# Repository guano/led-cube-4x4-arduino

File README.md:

# led-cube-4x4-arduino
This is all the files for my 4x4 led cube, programmed by arduino. Also has a pcb design file for to make it a shield.

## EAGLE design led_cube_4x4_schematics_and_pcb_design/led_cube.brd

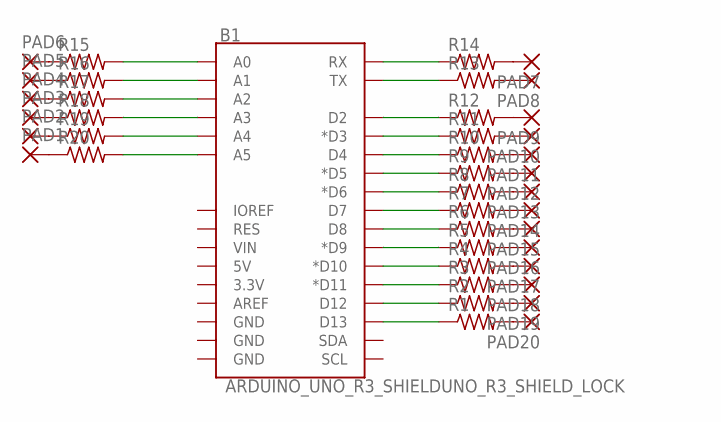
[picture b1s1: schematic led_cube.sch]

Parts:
B1: ARDUINO_UNO_R3_SHIELDUNO_R3_SHIELD_LOCK; UNO_R3_SHIELD_LOCK
PAD1, PAD2, PAD3, PAD4, PAD5, PAD6, PAD7, PAD8, PAD9, PAD10, PAD11, PAD12, PAD13, PAD14, PAD15, PAD16, PAD17, PAD18, PAD19, PAD20: 3,81/1,1
R1, R2, R3, R4, R5, R6, R7, R8, R9, R10, R11, R12, R13, R14, R15, R16, R17, R18, R19, R20: R-US_0204/7; 0204/7

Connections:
unnamed: PAD1.1, R20.1
unnamed: PAD2.1, R19.1
unnamed: PAD3.1, R18.1
unnamed: PAD4.1, R17.1
unnamed: PAD5.1, R16.1
unnamed: PAD6.1, R15.1
unnamed: PAD7.1, R14.2
unnamed: PAD8.1, R13.2
unnamed: PAD9.1, R12.2
unnamed: PAD10.1, R11.2
unnamed: PAD11.1, R10.2
unnamed: PAD12.1, R9.2
unnamed: PAD13.1, R8.2
unnamed: PAD14.1, R7.2
unnamed: PAD15.1, R6.2
unnamed: PAD16.1, R5.2
unnamed: PAD17.1, R4.2
unnamed: PAD18.1, R3.2
unnamed: PAD19.1, R2.2
unnamed: PAD20.1, R1.2
unnamed: B1.A0, R15.2
unnamed: B1.A1, R16.2
unnamed: B1.A2, R17.2
unnamed: B1.A3, R18.2
unnamed: B1.A4, R19.2
unnamed: B1.A5, R20.2
unnamed: B1.RX, R14.1
unnamed: B1.TX, R13.1
unnamed: B1.D2, R12.1
unnamed: B1.D3 (*D3), R11.1
unnamed: B1.D4, R10.1
unnamed: B1.D5 (*D5), R9.1
unnamed: B1.D6 (*D6), R8.1
unnamed: B1.D7, R7.1
unnamed: B1.D8, R6.1
unnamed: B1.D9 (*D9), R5.1
unnamed: B1.D10 (*D10), R4.1
unnamed: B1.D11 (*D11), R3.1
unnamed: B1.D12, R2.1
unnamed: B1.D13, R1.1

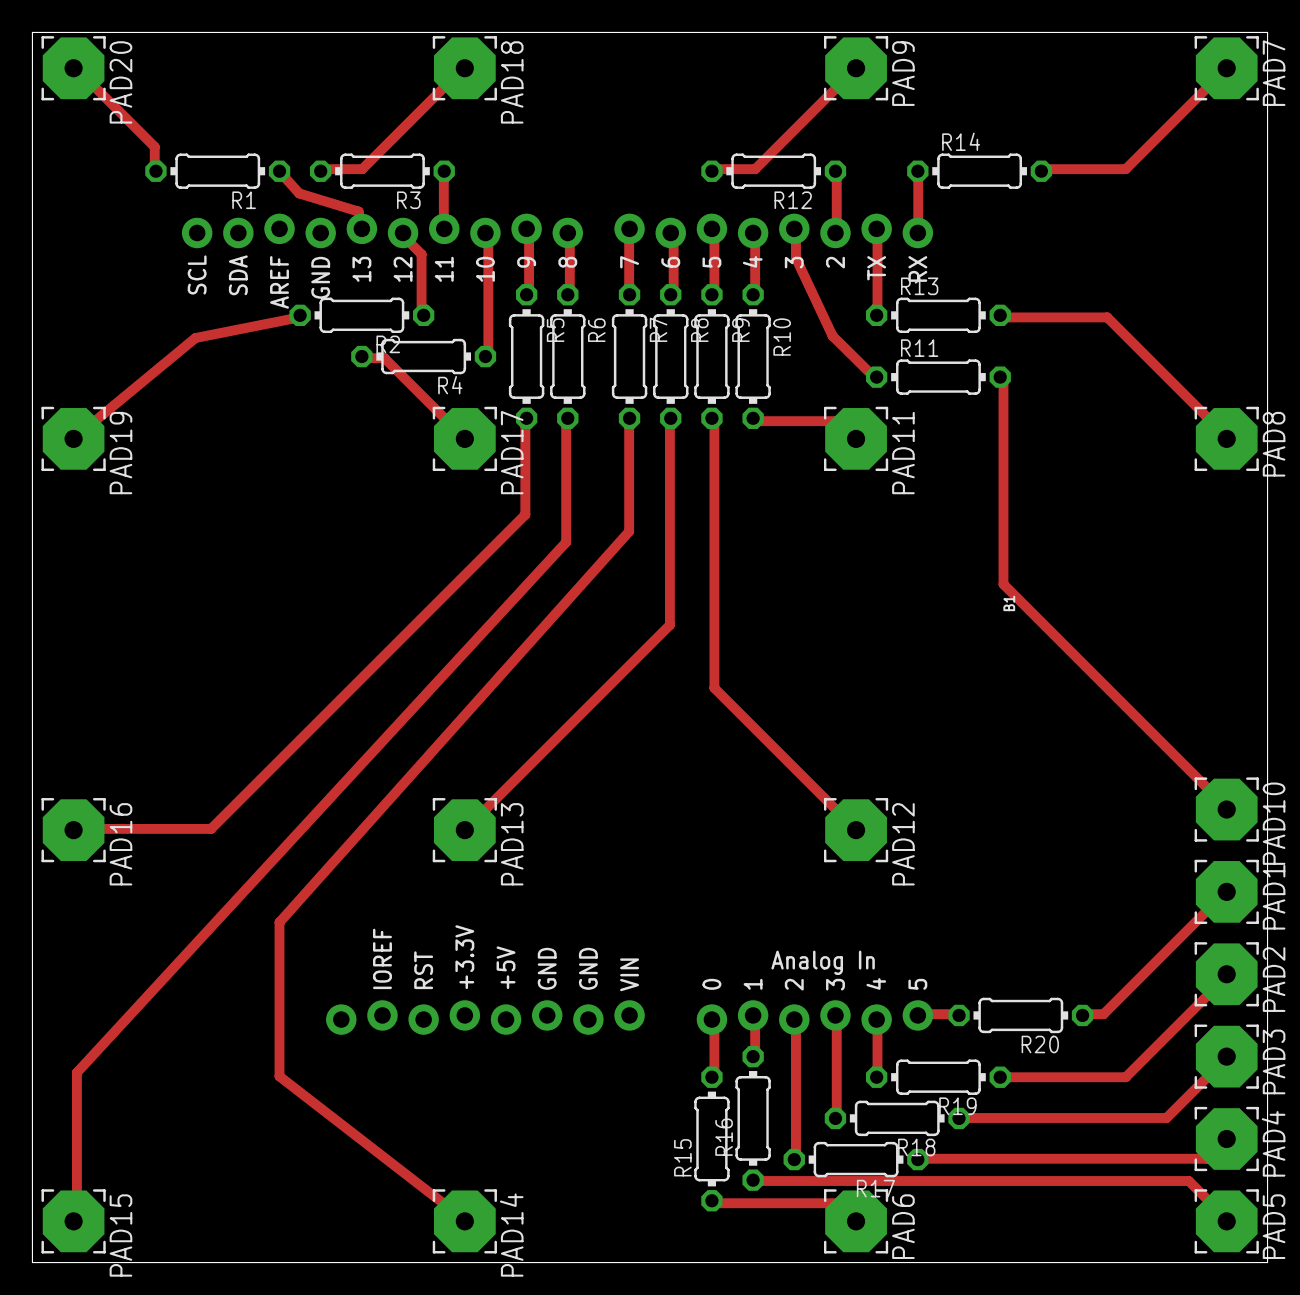
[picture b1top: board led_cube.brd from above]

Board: 2 copper layers, 76.2 x 75.9 mm, 41 parts (0 on the bottom side), 40 nets.

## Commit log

2017-02-24 This will make it so that the eagle files do not have LF changed to CRLF. I do not know if that will cause a problem, so we will just avoid it.
2017-02-24 All the schematics and pcb design for the 4x4 cube
2017-02-24 added the sample code, edited quite a bit. Currently just lights up the top row of lights. Better code to arrive
2017-03-02 started putting in what I want changed
2017-03-07 Finally got a neat animation going! more complicated ones to come

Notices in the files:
parts and their libraries:
SparkFun-Boards: Licensing: Creative Commons ShareAlike 4.0 International - https://creativecommons.org/licenses/by-sa/4.0
